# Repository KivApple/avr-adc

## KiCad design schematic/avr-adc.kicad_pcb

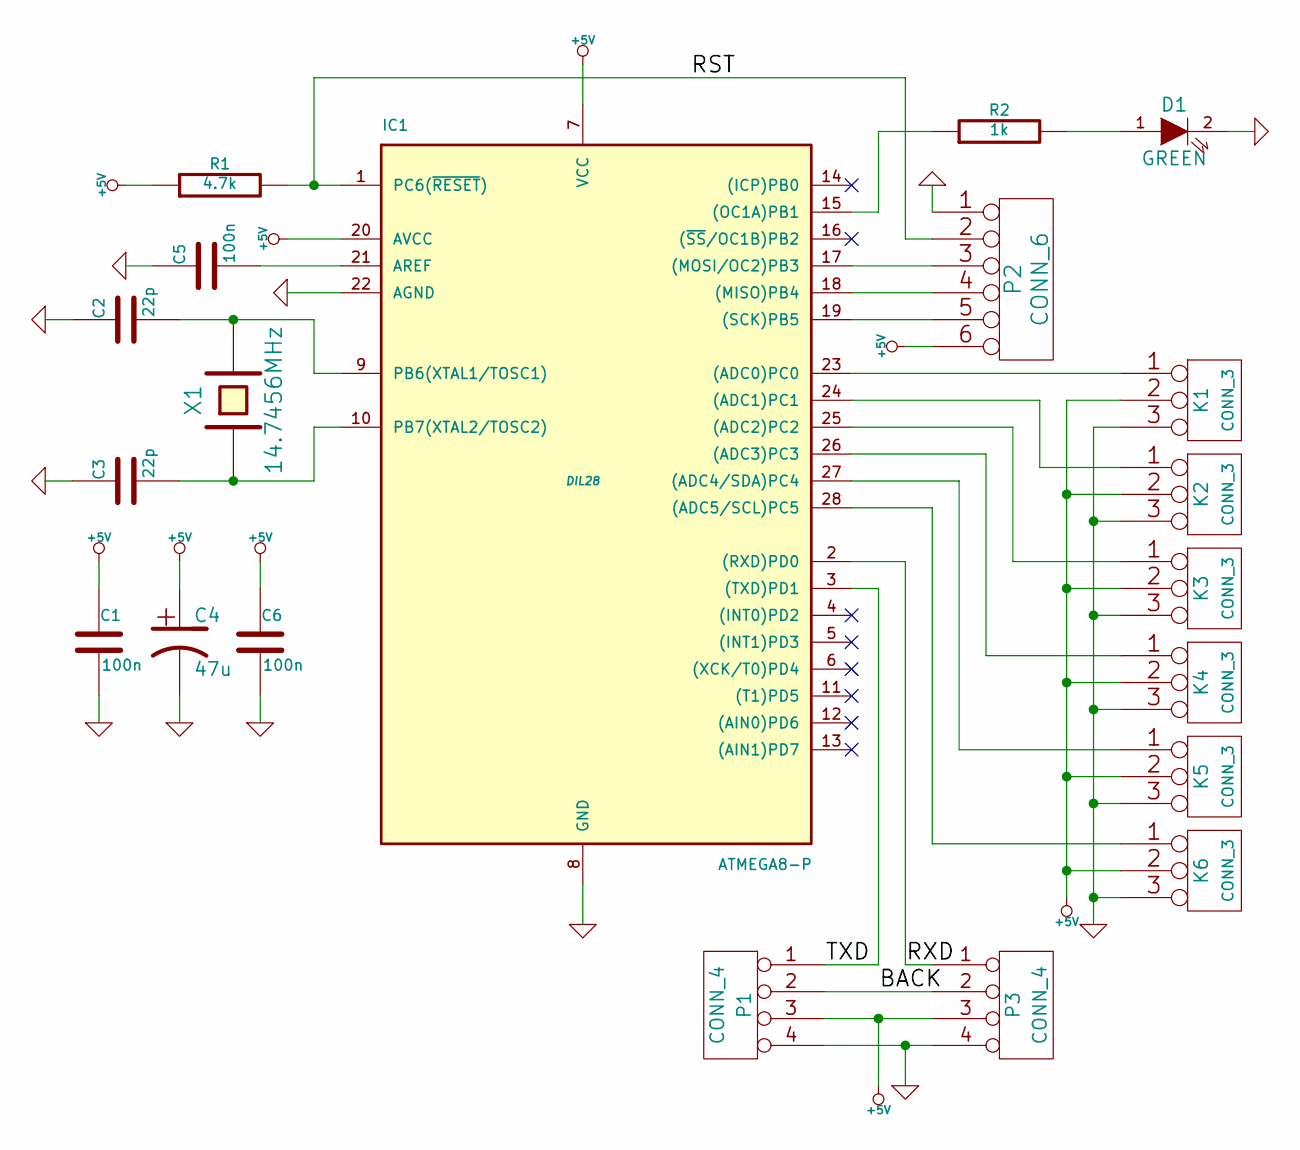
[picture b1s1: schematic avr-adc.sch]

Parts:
C1, C5, C6: 100n
C2, C3: 22p
C4: 47u
D1: GREEN
IC1: ATMEGA8-P; DIL28
K1, K2, K3, K4, K5, K6: CONN_3
P1, P3: CONN_4
P2: CONN_6
R1: 4.7k
R2: 1k
X1: 14.7456MHz

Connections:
+5V: C1.1, C4.1, C6.1, IC1.7 (VCC), IC1.20 (AVCC), K1.2 (PM), K2.2 (PM), K3.2 (PM), K4.2 (PM), K5.2 (PM), K6.2 (PM), P1.3, P2.6, P3.3, R1.1
/BACK: P1.2, P3.2
/RST: IC1.1 (PC6(~RESET~)), P2.2, R1.2
/RXD: IC1.2 ((RXD)PD0), P3.1
/TXD: IC1.3 ((TXD)PD1), P1.1
GND: C1.2, C2.1, C3.1, C4.2, C5.1, C6.2, D1.2 (K), IC1.8 (GND), IC1.22 (AGND), K1.3, K2.3, K3.3, K4.3, K5.3, K6.3, P1.4, P2.1, P3.4
unnamed: IC1.26 ((ADC3)PC3), K4.1
unnamed: IC1.25 ((ADC2)PC2), K3.1
unnamed: IC1.24 ((ADC1)PC1), K2.1
unnamed: IC1.15 ((OC1A)PB1), R2.1
unnamed: D1.1 (A), R2.2
unnamed: IC1.28 ((ADC5/SCL)PC5), K6.1
unnamed: IC1.27 ((ADC4/SDA)PC4), K5.1
unnamed: IC1.23 ((ADC0)PC0), K1.1
unnamed: IC1.17 ((MOSI/OC2)PB3), P2.3
unnamed: IC1.18 ((MISO)PB4), P2.4
unnamed: IC1.19 ((SCK)PB5), P2.5
unnamed: C5.2, IC1.21 (AREF)
unnamed: C3.2, IC1.10 (PB7(XTAL2/TOSC2)), X1.1
unnamed: C2.2, IC1.9 (PB6(XTAL1/TOSC1)), X1.2

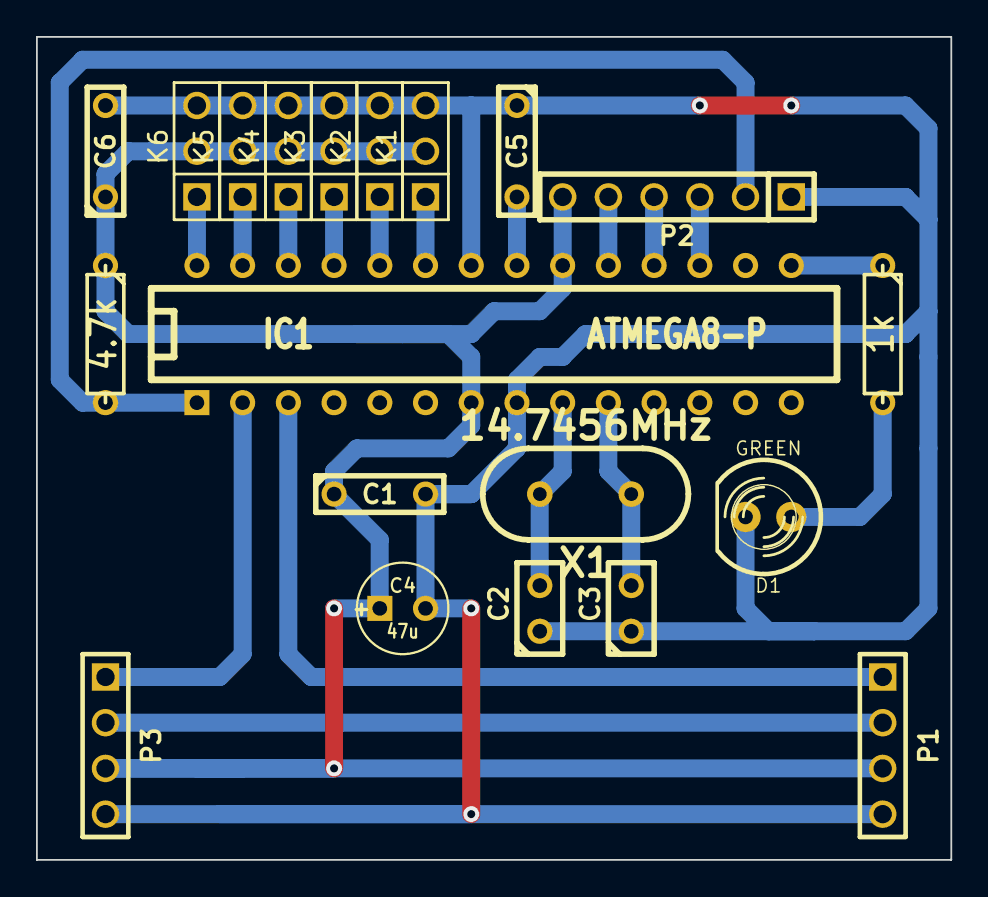
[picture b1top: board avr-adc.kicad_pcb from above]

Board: 2 copper layers, 50.8 x 45.7 mm, 20 parts (0 on the bottom side), 20 nets.

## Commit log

2014-10-07 First push
